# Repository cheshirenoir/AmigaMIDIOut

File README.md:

# AmigaMIDIOut
The Amiga MIDI Out is a simple MIDI interface for the Amiga serial port, designed for MIDI out only. 
This is based on a design from Grzegorz Kraszewski (https://rastport.com) and all credit and no responsibility should go to Grzegorz. This design with permission. All support for THIS product is only supplied by me. Do NOT hassle Grzegorz. DO go and buy their products. Especially if you want MIDI In.

CC BY SA

Amiga MIDI Library is here: https://aminet.net/package/mus/midi/camd

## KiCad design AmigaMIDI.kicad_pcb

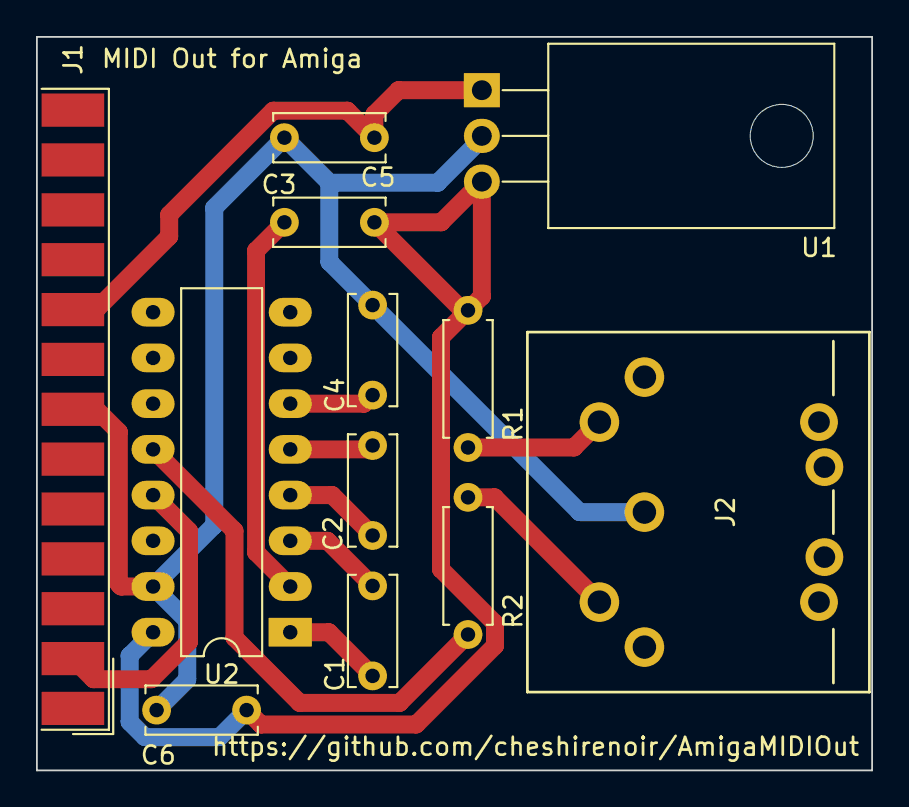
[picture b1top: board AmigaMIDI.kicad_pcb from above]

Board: 2 copper layers, 46.4 x 40.8 mm, 12 parts (0 on the bottom side), 13 nets.

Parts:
C1, C2, C3, C4, C5, C6: 100nF; C_Disc_D6.0mm_W2.5mm_P5.00mm
J1: DB25_Female; DSUB-25_Female_EdgeMount_P2.77mm
J2: DIN-5_180degree; DIN-5-Variable
R1, R2: 220; R_Axial_DIN0207_L6.3mm_D2.5mm_P7.62mm_Horizontal
U1: LM78M05_TO220; TO-220-3_Horizontal_TabDown
U2: MAX232; DIP-16_W7.62mm_LongPads

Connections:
+5V: C3.2, C6.1, R1.2, U1.3 (VO), U2.16 (VCC)
GND: C4.2, C5.2, C6.2, J1.7, J2.2, U1.2 (GND), U2.15 (GND)
unnamed: C1.1, U2.1 (C1+)
unnamed: C1.2, U2.3 (C1-)
unnamed: C2.1, U2.4 (C2+)
unnamed: C2.2, U2.5 (C2-)
unnamed: C3.1, U2.2 (VS+)
unnamed: C4.1, U2.6 (VS-)
unnamed: C5.1, J1.9, U1.1 (VI)
unnamed: J1.2, U2.13 (R1IN)
unnamed: J2.4, R1.1
unnamed: J2.5, R2.2
unnamed: R2.1, U2.12 (R1OUT)

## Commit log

2022-07-31 Add files via upload
    First version
